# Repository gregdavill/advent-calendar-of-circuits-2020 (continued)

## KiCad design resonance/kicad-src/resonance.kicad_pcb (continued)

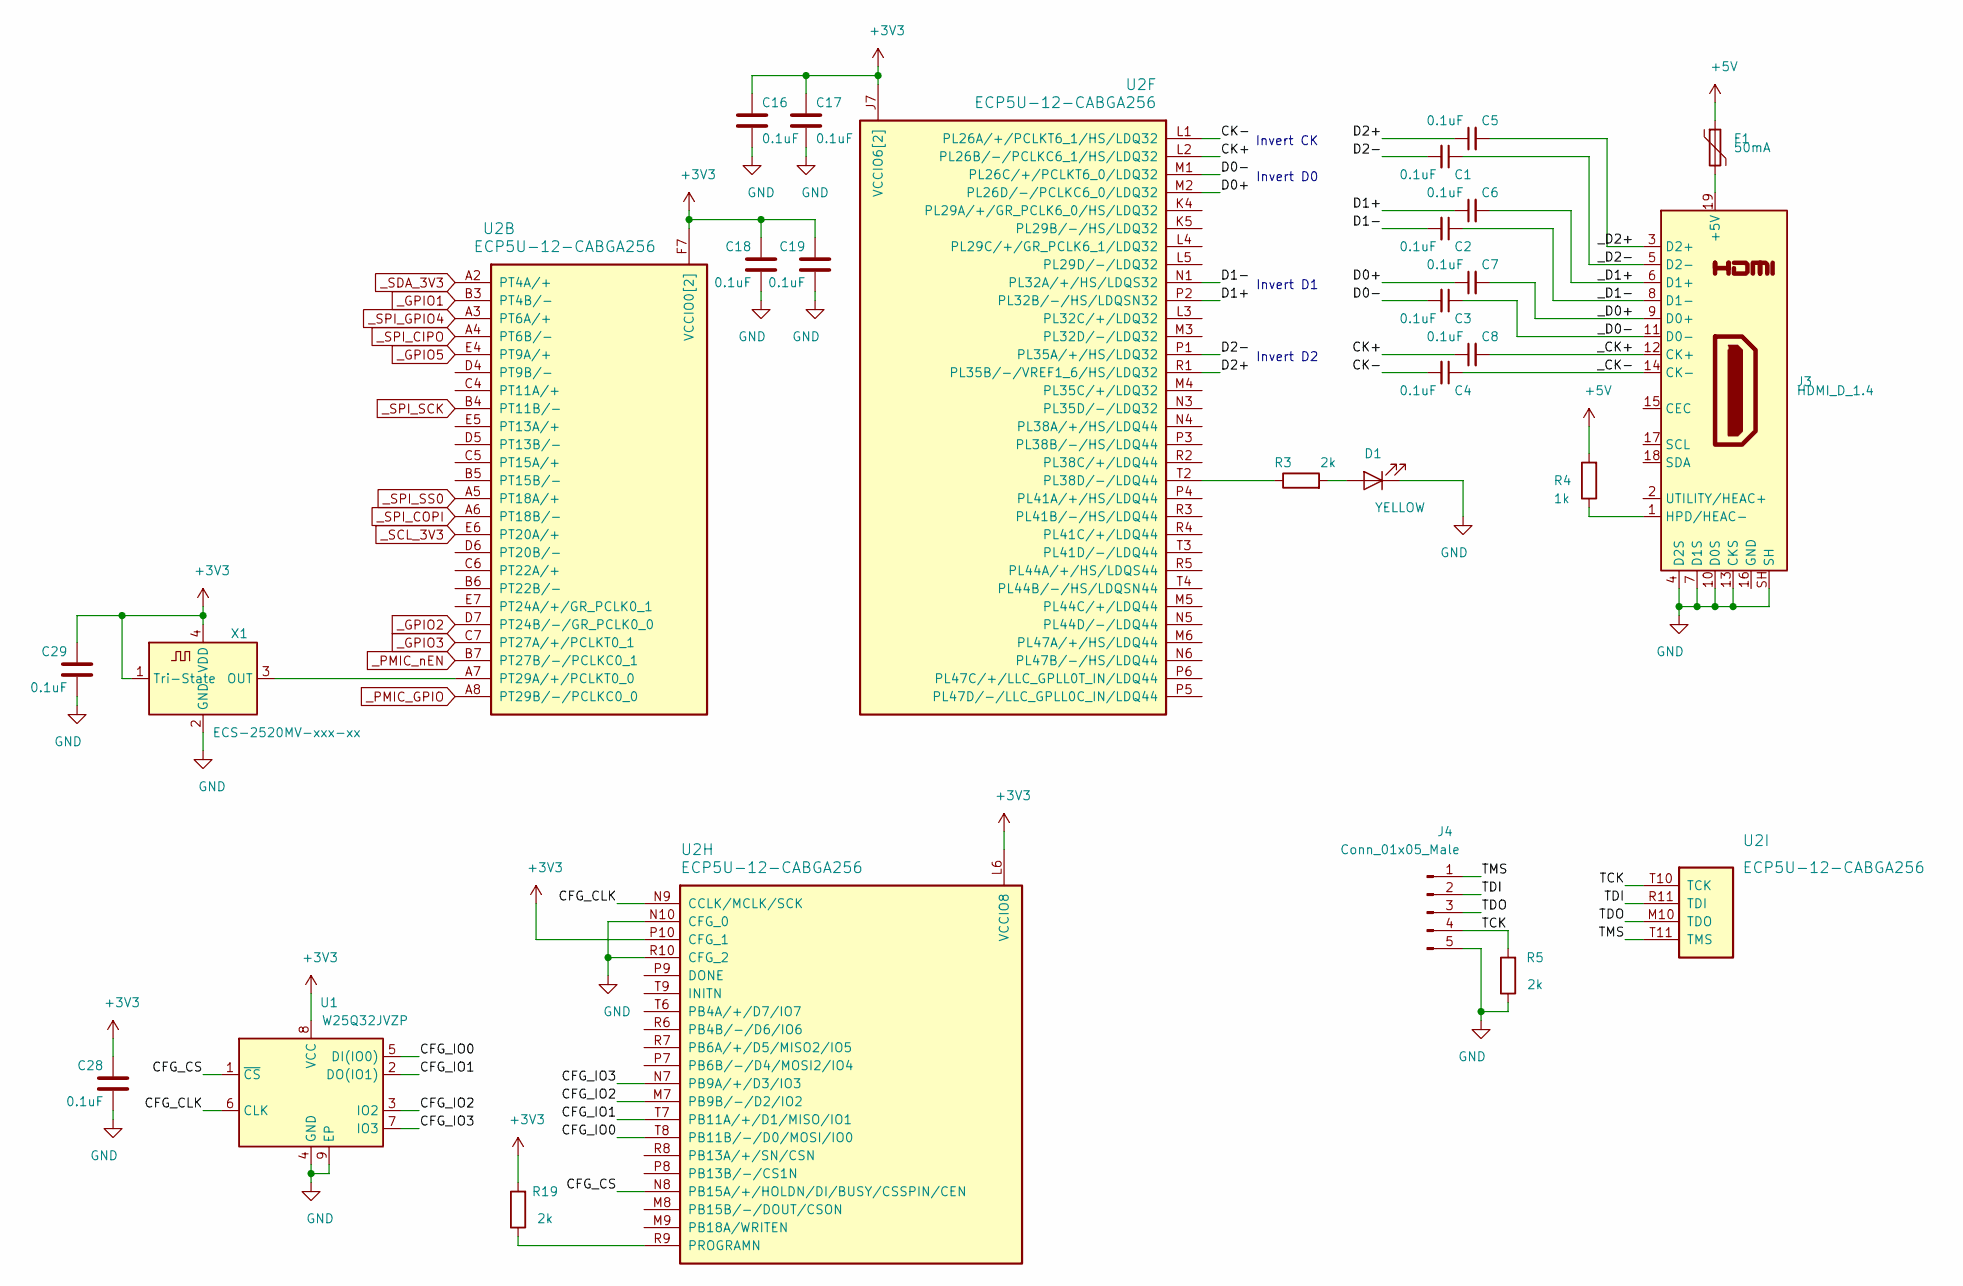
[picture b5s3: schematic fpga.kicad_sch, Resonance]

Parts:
C1, C2, C3, C4, C5, C6, C7, C8, C16, C17, C18, C19, C28, C29: 0.1uF; C_0402_1005Metric
D1: YELLOW; LED_0603_1608Metric
F1: 50mA; Fuse_0805_2012Metric
J3: HDMI_D_1.4; HDMI_Micro-D_Molex_46765-1x01
J4: Conn_01x05_Male; PinHeader_1x05_P2.54mm_Vertical
R3, R5, R19: 2k; R_0402_1005Metric
R4: 1k; R_0402_1005Metric
U1: W25Q32JVZP; WSON-8-1EP_6x5mm_P1.27mm_EP3.4x4.3mm
U2: ECP5U-12-CABGA256; BGA-256_14.0x14.0mm_Layout16x16_P0.8mm_Ball0.45mm_Pad0.32mm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
X1: ECS-2520MV-xxx-xx; Oscillator_SMD_ECS_2520MV-xxx-xx-4Pin_2.5x2.0mm

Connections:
+3V3: C16.1, C17.1, C18.1, C19.1, C28.1, C29.1, R19.2, U1.8 (VCC), U2.F6 (VCCIO0[2]), U2.F7 (VCCIO0[2]), U2.J6 (VCCIO6[2]), U2.J7 (VCCIO6[2]), U2.L6 (VCCIO8), U2.P10 (CFG_1), X1.1 (Tri-State), X1.4 (VDD); also elsewhere on the board
+5V: F1.1, R4.2; also elsewhere on the board
/fpga/CFG_CLK: U1.6 (CLK), U2.N9 (CCLK/MCLK/SCK)
/fpga/CFG_CS: U1.1 (~CS), U2.N8 (PB15A/+/HOLDN/DI/BUSY/CSSPIN/CEN)
/fpga/CFG_IO0: U1.5 (DI(IO0)), U2.T8 (PB11B/-/D0/MOSI/IO0)
/fpga/CFG_IO1: U1.2 (DO(IO1)), U2.T7 (PB11A/+/D1/MISO/IO1)
/fpga/CFG_IO2: U1.3 (IO2), U2.M7 (PB9B/-/D2/IO2)
/fpga/CFG_IO3: U1.7 (IO3), U2.N7 (PB9A/+/D3/IO3)
/fpga/CK+: C8.1, U2.L2 (PL26B/-/PCLKC6_1/HS/LDQ32)
/fpga/CK-: C4.2, U2.L1 (PL26A/+/PCLKT6_1/HS/LDQ32)
/fpga/D0+: C7.1, U2.M2 (PL26D/-/PCLKC6_0/LDQ32)
/fpga/D0-: C3.2, U2.M1 (PL26C/+/PCLKT6_0/LDQ32)
/fpga/D1+: C6.1, U2.P2 (PL32B/-/HS/LDQSN32)
/fpga/D1-: C2.2, U2.N1 (PL32A/+/HS/LDQS32)
/fpga/D2+: C5.1, U2.R1 (PL35B/-/VREF1_6/HS/LDQ32)
/fpga/D2-: C1.2, U2.P1 (PL35A/+/HS/LDQ32)
/fpga/TCK: J4.4, R5.2, U2.T10 (TCK)
/fpga/TDI: J4.2, U2.R11 (TDI)
/fpga/TDO: J4.3, U2.M10 (TDO)
/fpga/TMS: J4.1, U2.T11 (TMS)
/fpga/_CK+: C8.2, J3.12 (CK+)
/fpga/_CK-: C4.1, J3.14 (CK-)
/fpga/_D0+: C7.2, J3.9 (D0+)
/fpga/_D0-: C3.1, J3.11 (D0-)
/fpga/_D1+: C6.2, J3.6 (D1+)
/fpga/_D1-: C2.1, J3.8 (D1-)
/fpga/_D2+: C5.2, J3.3 (D2+)
/fpga/_D2-: C1.1, J3.5 (D2-)
GND: C16.2, C17.2, C18.2, C19.2, C28.2, C29.2, D1.1 (K), J3.4 (D2S), J3.7 (D1S), J3.10 (D0S), J3.13 (CKS), J3.SH, J4.5, R5.1, U1.4 (GND), U1.9 (EP), U2.N10 (CFG_0), U2.R10 (CFG_2), X1.2 (GND); also elsewhere on the board
unnamed: D1.2 (A), R3.2
unnamed: J3.1 (HPD/HEAC-), R4.1
unnamed: F1.2, J3.19 (+5V)
unnamed: U2.A7 (PT29A/+/PCLKT0_0), X1.3 (OUT)
unnamed: R19.1, U2.R9 (PROGRAMN)
unnamed: R3.1, U2.T2 (PL38D/-/LDQ44)
_GPIO1: U2.B3 (PT4B/-); also elsewhere on the board
_GPIO2: U2.D7 (PT24B/-/GR_PCLK0_0); also elsewhere on the board
_GPIO3: U2.C7 (PT27A/+/PCLKT0_1); also elsewhere on the board
_GPIO5: U2.E4 (PT9A/+); also elsewhere on the board
_PMIC_GPIO: U2.A8 (PT29B/-/PCLKC0_0); also elsewhere on the board
_PMIC_nEN: U2.B7 (PT27B/-/PCLKC0_1); also elsewhere on the board
_SCL_3V3: U2.E6 (PT20A/+); also elsewhere on the board
_SDA_3V3: U2.A2 (PT4A/+); also elsewhere on the board
_SPI_CIPO: U2.A4 (PT6B/-); also elsewhere on the board
_SPI_COPI: U2.A6 (PT18B/-); also elsewhere on the board
_SPI_GPIO4: U2.A3 (PT6A/+); also elsewhere on the board
_SPI_SCK: U2.B4 (PT11B/-); also elsewhere on the board
_SPI_SS0: U2.A5 (PT18A/+); also elsewhere on the board

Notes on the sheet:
Invert CK
Invert D0
Invert D1
Invert D2

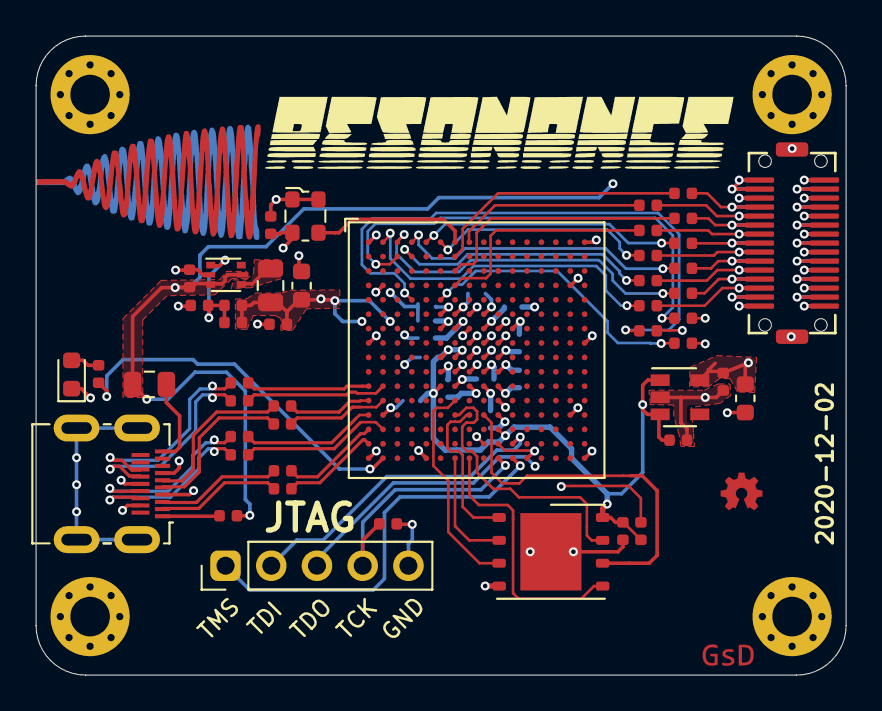
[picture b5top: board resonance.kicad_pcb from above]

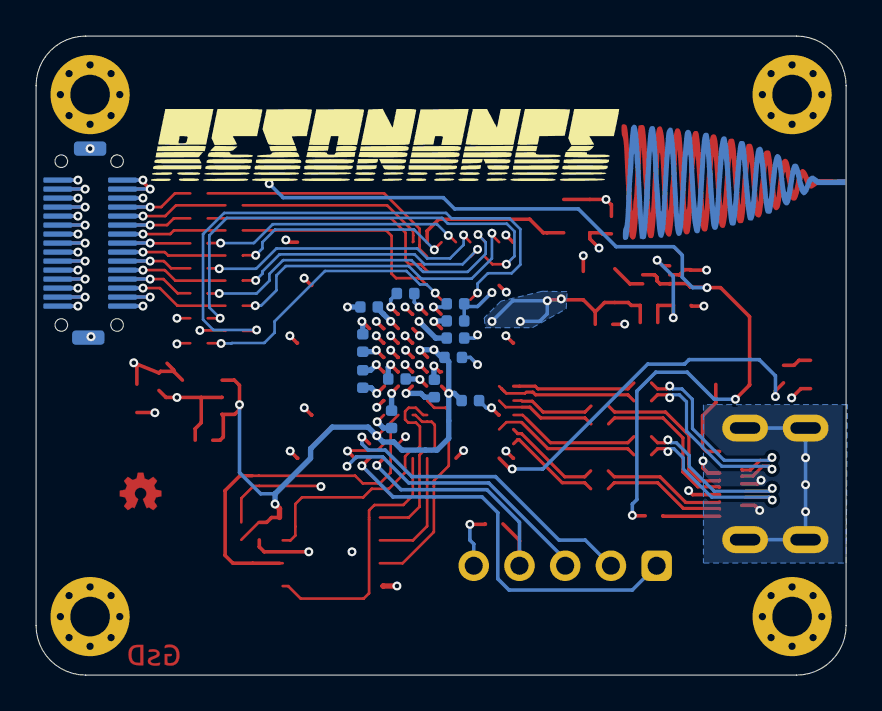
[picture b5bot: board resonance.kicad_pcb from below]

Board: 4 copper layers, 45.0 x 35.5 mm, 66 parts (13 on the bottom side), 75 nets.

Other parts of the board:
H1, H4: ECG_VCM; MountingHole_2.2mm_M2_Pad_Via
H2, H3: MountingHole_Pad; MountingHole_2.2mm_M2_Pad_Via
LOGO1: Q_NMOS_GSD; gsd_logo_small
LOGO2: Logo_Open_Hardware_Small; oshw_small

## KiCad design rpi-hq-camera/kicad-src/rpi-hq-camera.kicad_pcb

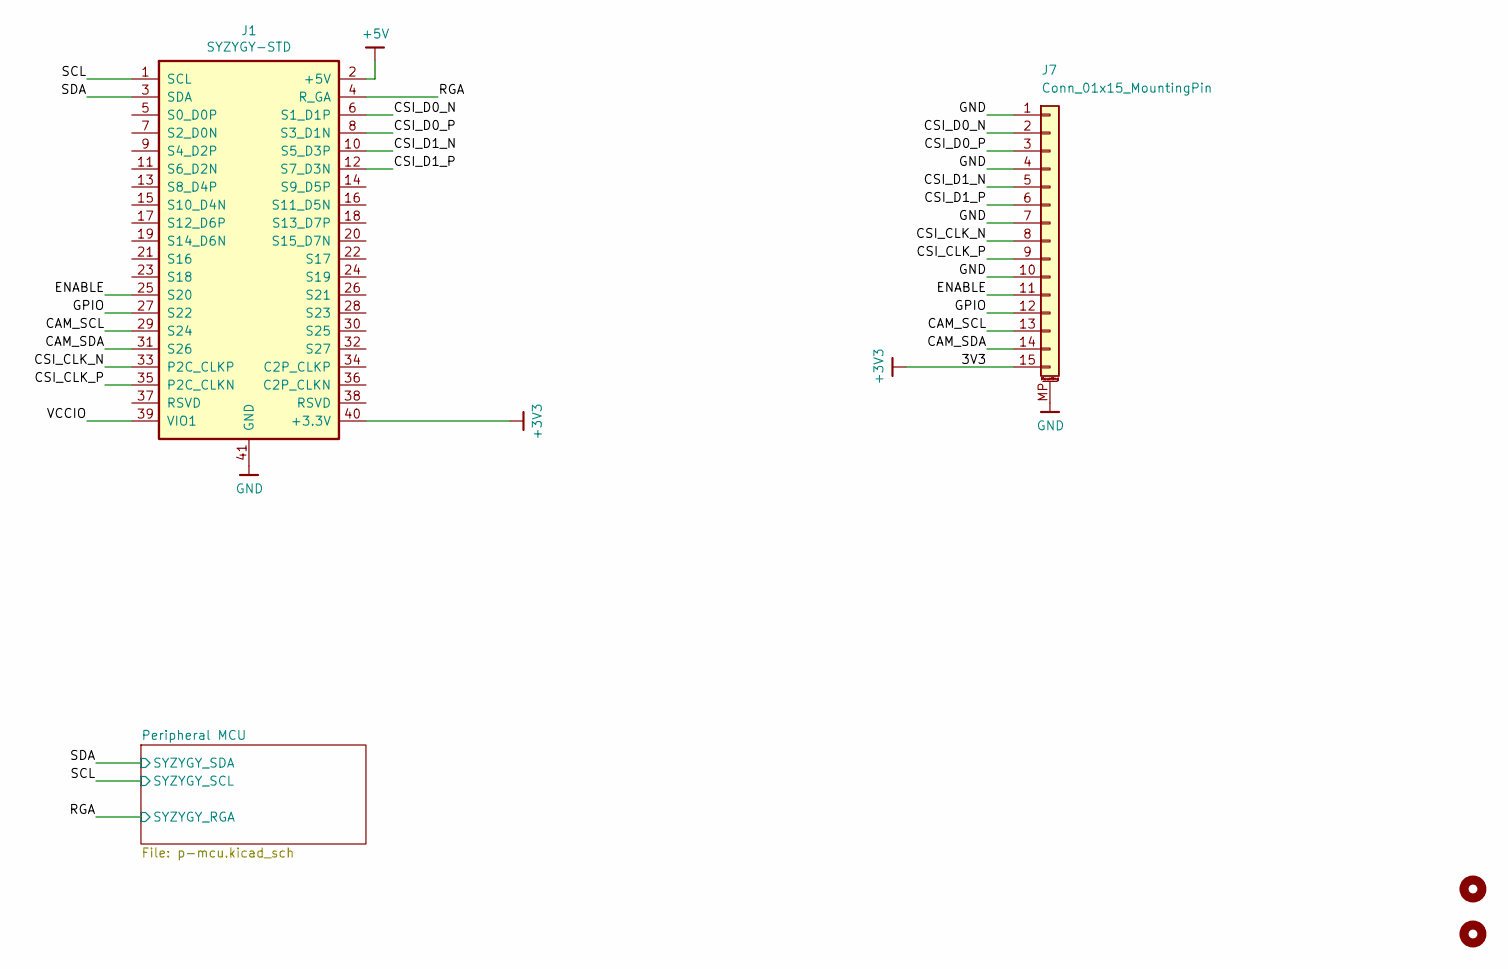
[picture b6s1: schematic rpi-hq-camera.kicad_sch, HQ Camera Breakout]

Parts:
H1, H2: MountingHole; MountingHole_3.2mm_M3_DIN965
J1: SYZYGY-STD; SYZYGY-STD-POD
J7: Conn_01x15_MountingPin; FCI_SFW15R-1STE1LF_1x15-1MP_P1.00mm_Horizontal

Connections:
+3V3: J1.40 (+3.3V), J7.15; also elsewhere on the board
+5V: J1.2 (+5V)
/CAM_SCL: J1.29 (S24), J7.13
/CAM_SDA: J1.31 (S26), J7.14
/CSI_CLK_N: J1.33 (P2C_CLKP), J7.8
/CSI_CLK_P: J1.35 (P2C_CLKN), J7.9
/CSI_D0_N: J1.6 (S1_D1P), J7.2
/CSI_D0_P: J1.8 (S3_D1N), J7.3
/CSI_D1_N: J1.10 (S5_D3P), J7.5
/CSI_D1_P: J1.12 (S7_D3N), J7.6
/ENABLE: J1.25 (S20), J7.11
/GPIO: J1.27 (S22), J7.12
/RGA: J1.4 (R_GA); also elsewhere on the board
/SCL: J1.1 (SCL); also elsewhere on the board
/SDA: J1.3 (SDA); also elsewhere on the board
/VCCIO: J1.39 (VIO1)
GND: J1.41 (GND), J7.1, J7.4, J7.7, J7.10, J7.MP (MountPin); also elsewhere on the board

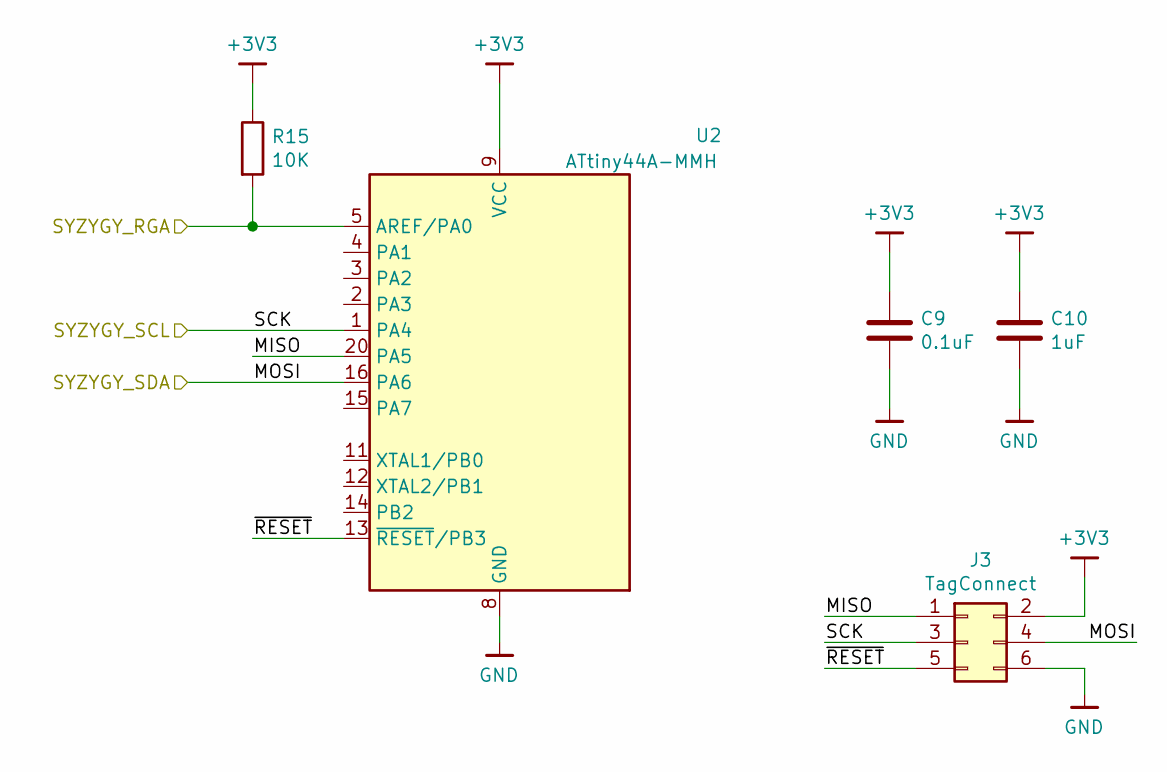
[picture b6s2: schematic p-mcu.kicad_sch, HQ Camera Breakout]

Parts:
C9: 0.1uF; C_0402_1005Metric
C10: 1uF; C_0402_1005Metric
J3: TagConnect; TC2030-NL_SMALL
R15: 10K; R_0402_1005Metric
U2: ATtiny44A-MMH; QFN-20-1EP_3x3mm_P0.45mm_EP1.6x1.6mm

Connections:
+3V3: C9.1, C10.1, J3.2, R15.1, U2.9 (VCC); also elsewhere on the board
/Peripheral MCU/MISO: J3.1, U2.20 (PA5)
/Peripheral MCU/~RESET: J3.5, U2.13 (~RESET~/PB3)
/RGA: R15.2, U2.5 (AREF/PA0); also elsewhere on the board
/SCL: J3.3, U2.1 (PA4); also elsewhere on the board
/SDA: J3.4, U2.16 (PA6); also elsewhere on the board
GND: C9.2, C10.2, J3.6, U2.8 (GND), U2.21 (GND); also elsewhere on the board
no_connect_51: U2.10 (NC)
no_connect_52: U2.17 (NC)
no_connect_53: U2.18 (NC)
no_connect_54: U2.19 (NC)
no_connect_55: U2.6 (NC)
no_connect_56: U2.7 (NC)

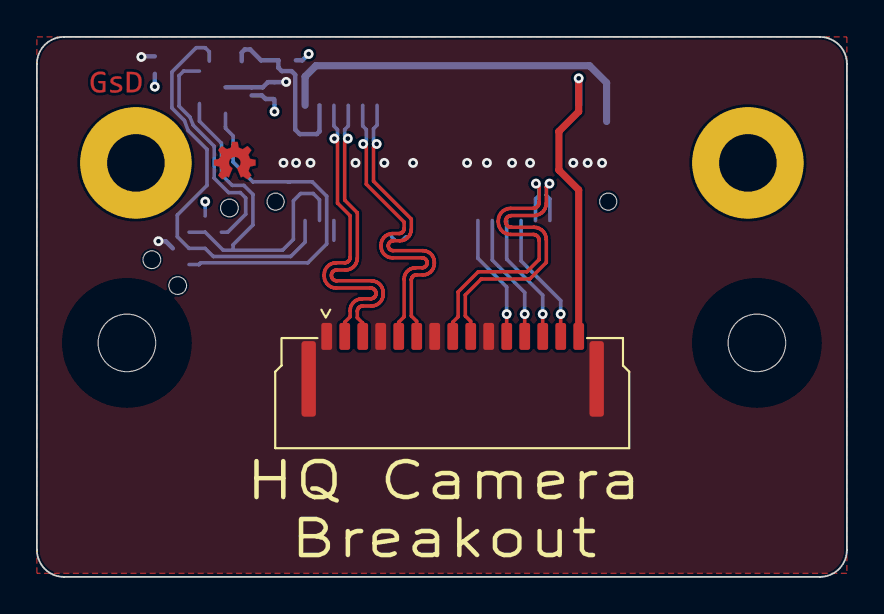
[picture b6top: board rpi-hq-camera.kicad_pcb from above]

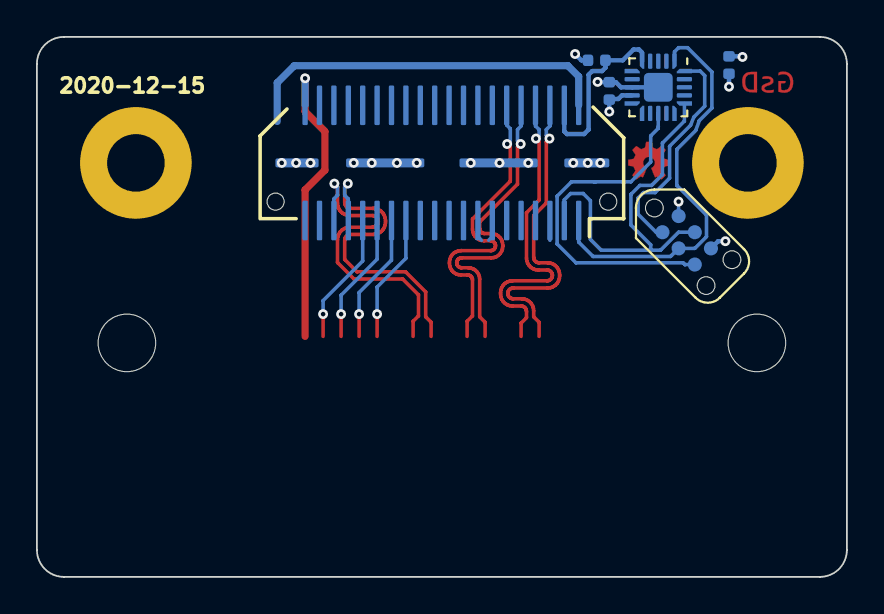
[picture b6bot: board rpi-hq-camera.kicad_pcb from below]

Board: 4 copper layers, 45.0 x 30.0 mm, 9 parts (6 on the bottom side), 17 nets.

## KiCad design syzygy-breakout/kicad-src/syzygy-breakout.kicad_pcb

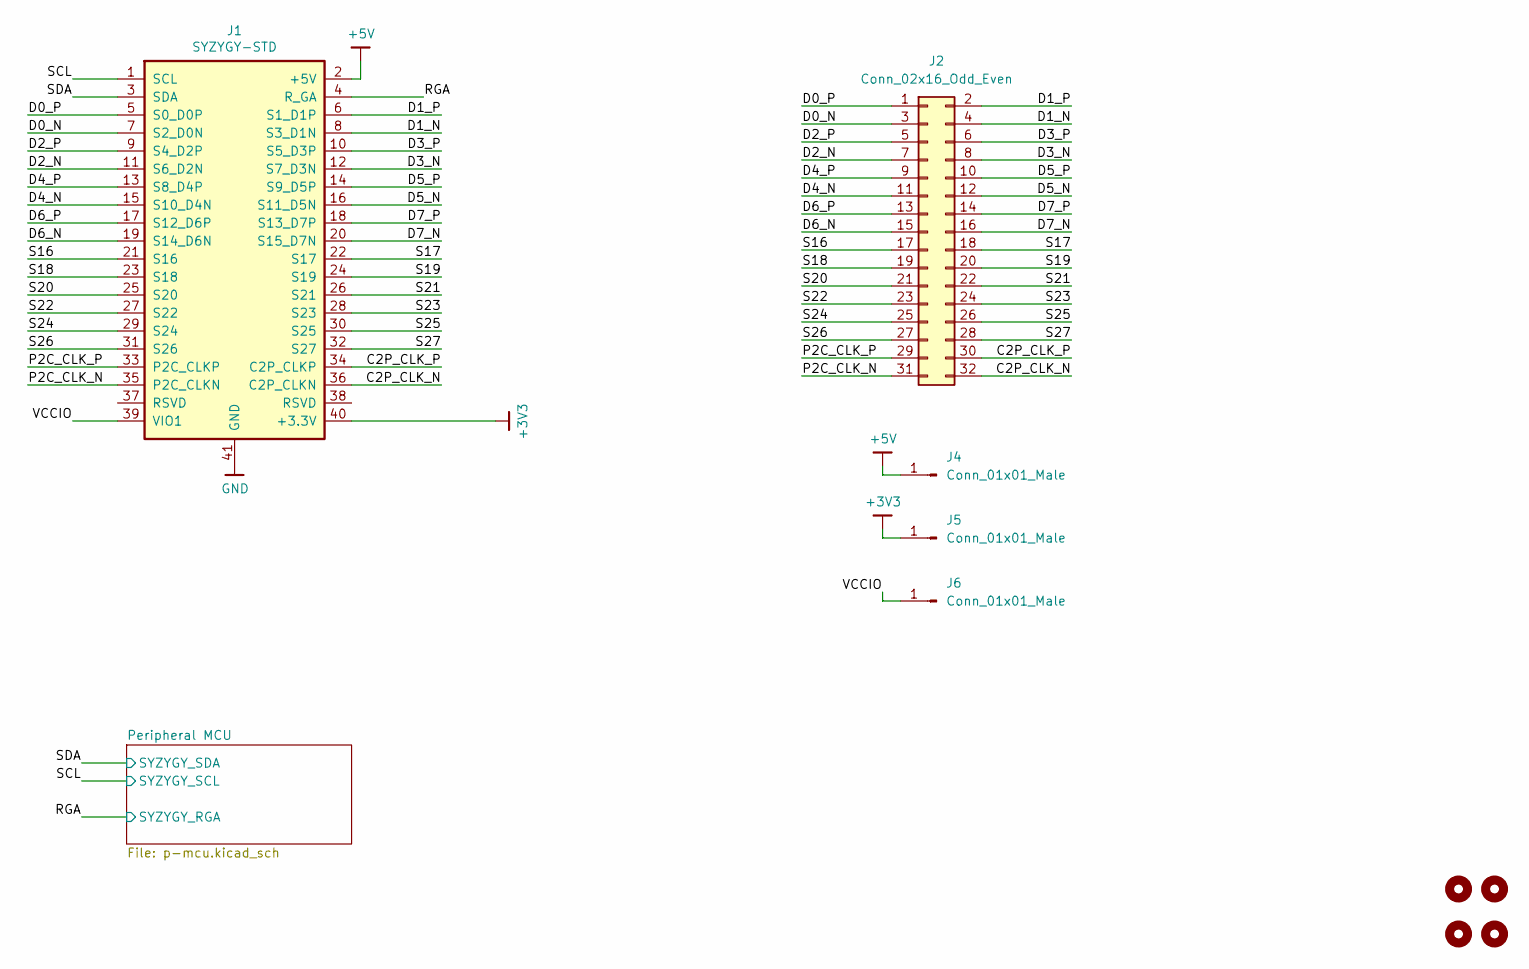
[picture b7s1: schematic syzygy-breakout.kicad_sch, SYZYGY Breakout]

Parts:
H1, H2, H3, H4: MountingHole; MountingHole_3.2mm_M3_DIN965
J1: SYZYGY-STD; SYZYGY-STD-POD
J2: Conn_02x16_Odd_Even; PinHeader_2x16_P2.54mm_Vertical
J4, J5, J6: Conn_01x01_Male; PinHeader_1x01_P2.54mm_Vertical

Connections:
+3V3: J1.40 (+3.3V), J5.1; also elsewhere on the board
+5V: J1.2 (+5V), J4.1
/C2P_CLK_N: J1.36 (C2P_CLKN), J2.32
/C2P_CLK_P: J1.34 (C2P_CLKP), J2.30
/D0_N: J1.7 (S2_D0N), J2.3
/D0_P: J1.5 (S0_D0P), J2.1
/D1_N: J1.8 (S3_D1N), J2.4
/D1_P: J1.6 (S1_D1P), J2.2
/D2_N: J1.11 (S6_D2N), J2.7
/D2_P: J1.9 (S4_D2P), J2.5
/D3_N: J1.12 (S7_D3N), J2.8
/D3_P: J1.10 (S5_D3P), J2.6
/D4_N: J1.15 (S10_D4N), J2.11
/D4_P: J1.13 (S8_D4P), J2.9
/D5_N: J1.16 (S11_D5N), J2.12
/D5_P: J1.14 (S9_D5P), J2.10
/D6_N: J1.19 (S14_D6N), J2.15
/D6_P: J1.17 (S12_D6P), J2.13
/D7_N: J1.20 (S15_D7N), J2.16
/D7_P: J1.18 (S13_D7P), J2.14
/P2C_CLK_N: J1.35 (P2C_CLKN), J2.31
/P2C_CLK_P: J1.33 (P2C_CLKP), J2.29
/RGA: J1.4 (R_GA); also elsewhere on the board
/S16: J1.21 (S16), J2.17
/S17: J1.22 (S17), J2.18
/S18: J1.23 (S18), J2.19
/S19: J1.24 (S19), J2.20
/S20: J1.25 (S20), J2.21
/S21: J1.26 (S21), J2.22
/S22: J1.27 (S22), J2.23
/S23: J1.28 (S23), J2.24
/S24: J1.29 (S24), J2.25
/S25: J1.30 (S25), J2.26
/S26: J1.31 (S26), J2.27
/S27: J1.32 (S27), J2.28
/SCL: J1.1 (SCL); also elsewhere on the board
/SDA: J1.3 (SDA); also elsewhere on the board
/VCCIO: J1.39 (VIO1), J6.1
GND: J1.41 (GND); also elsewhere on the board

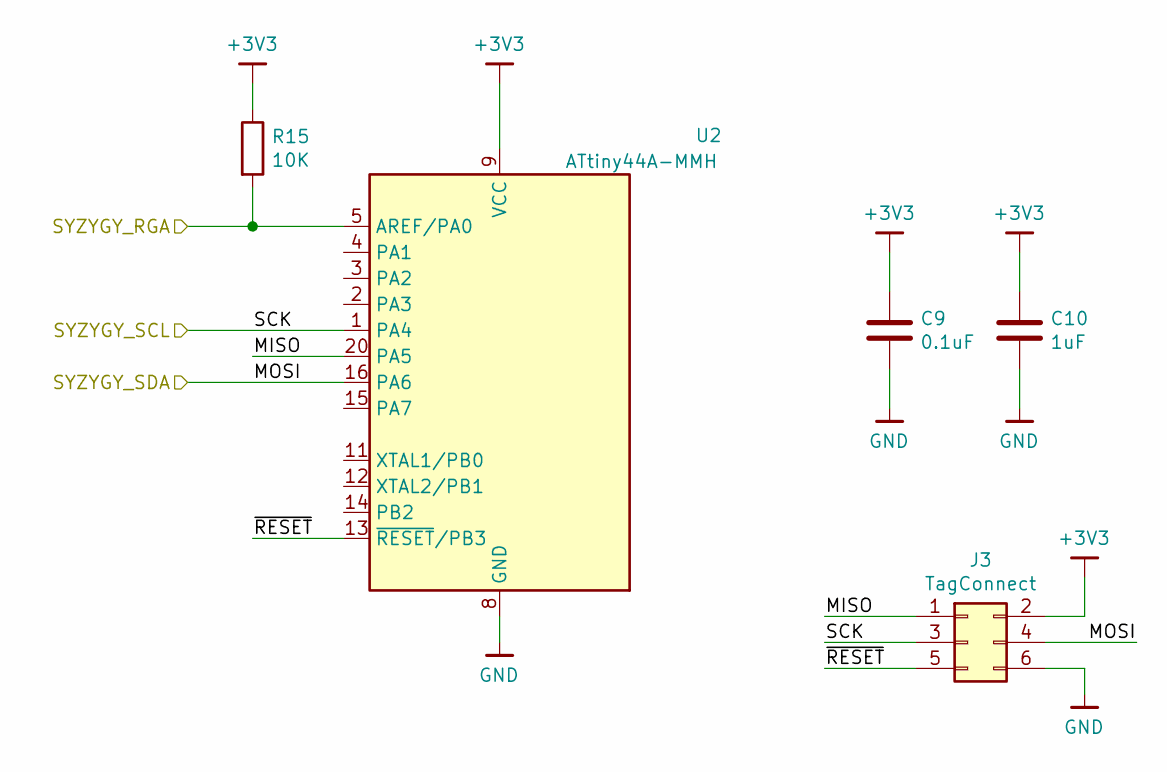
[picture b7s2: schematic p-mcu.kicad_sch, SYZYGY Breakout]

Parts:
C9: 0.1uF; C_0402_1005Metric
C10: 1uF; C_0402_1005Metric
J3: TagConnect; TC2030-NL_SMALL
R15: 10K; R_0402_1005Metric
U2: ATtiny44A-MMH; QFN-20-1EP_3x3mm_P0.45mm_EP1.6x1.6mm

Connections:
+3V3: C9.1, C10.1, J3.2, R15.1, U2.9 (VCC); also elsewhere on the board
/Peripheral MCU/MISO: J3.1, U2.20 (PA5)
/Peripheral MCU/~RESET: J3.5, U2.13 (~RESET~/PB3)
/RGA: R15.2, U2.5 (AREF/PA0); also elsewhere on the board
/SCL: J3.3, U2.1 (PA4); also elsewhere on the board
/SDA: J3.4, U2.16 (PA6); also elsewhere on the board
GND: C9.2, C10.2, J3.6, U2.8 (GND), U2.21 (GND); also elsewhere on the board
no_connect_51: U2.10 (NC)
no_connect_52: U2.17 (NC)
no_connect_53: U2.18 (NC)
no_connect_54: U2.19 (NC)
no_connect_55: U2.6 (NC)
no_connect_56: U2.7 (NC)

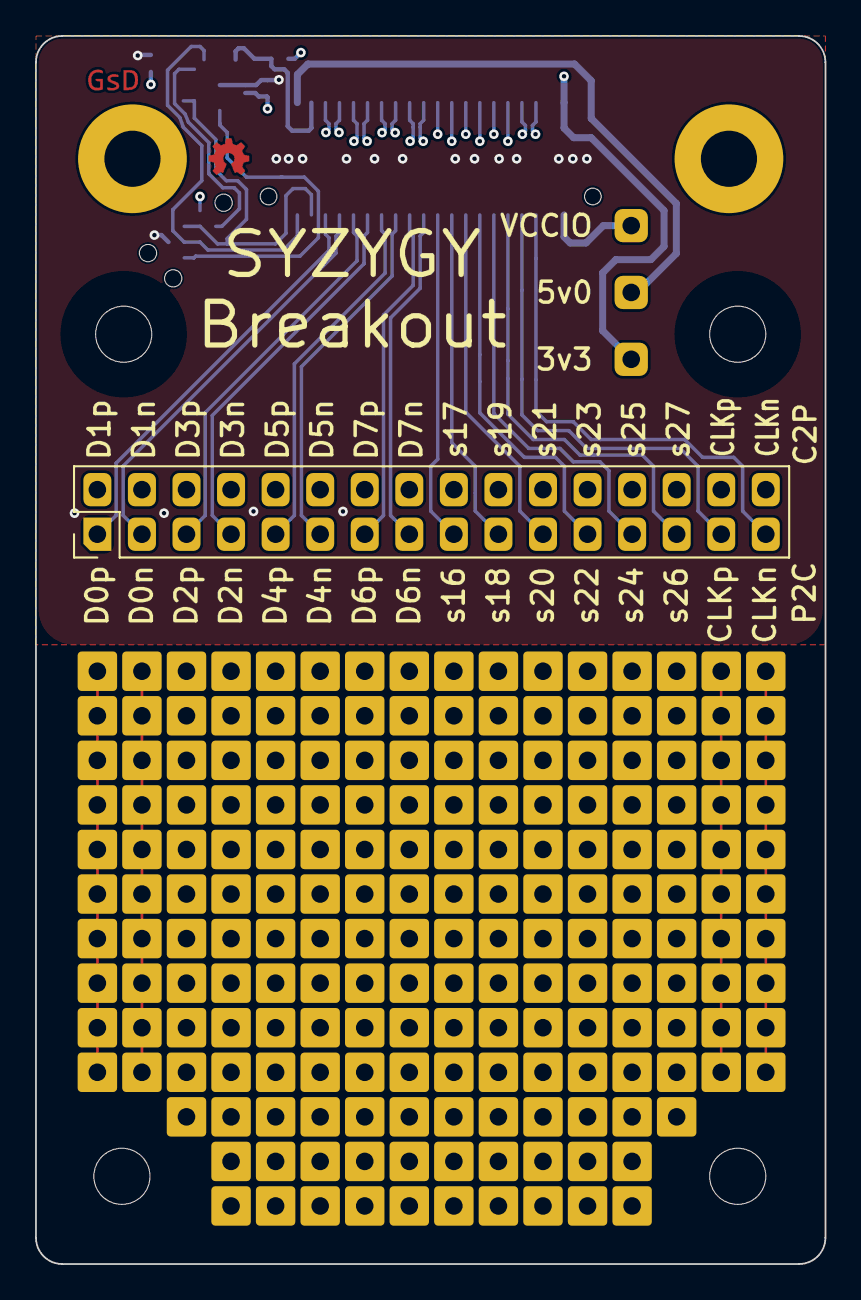
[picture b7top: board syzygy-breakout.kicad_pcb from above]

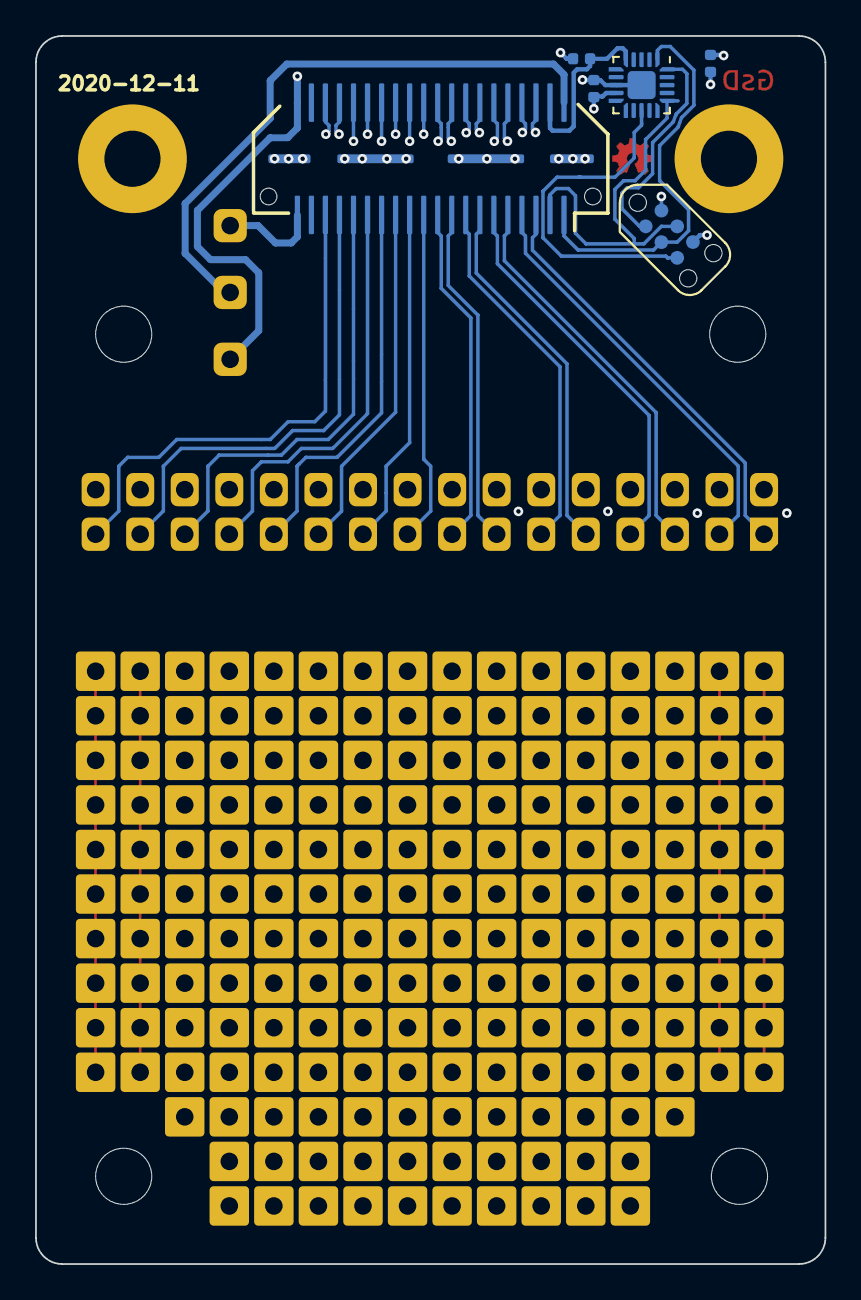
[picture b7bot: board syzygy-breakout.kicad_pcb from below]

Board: 4 copper layers, 45.0 x 70.0 mm, 14 parts (6 on the bottom side), 41 nets.

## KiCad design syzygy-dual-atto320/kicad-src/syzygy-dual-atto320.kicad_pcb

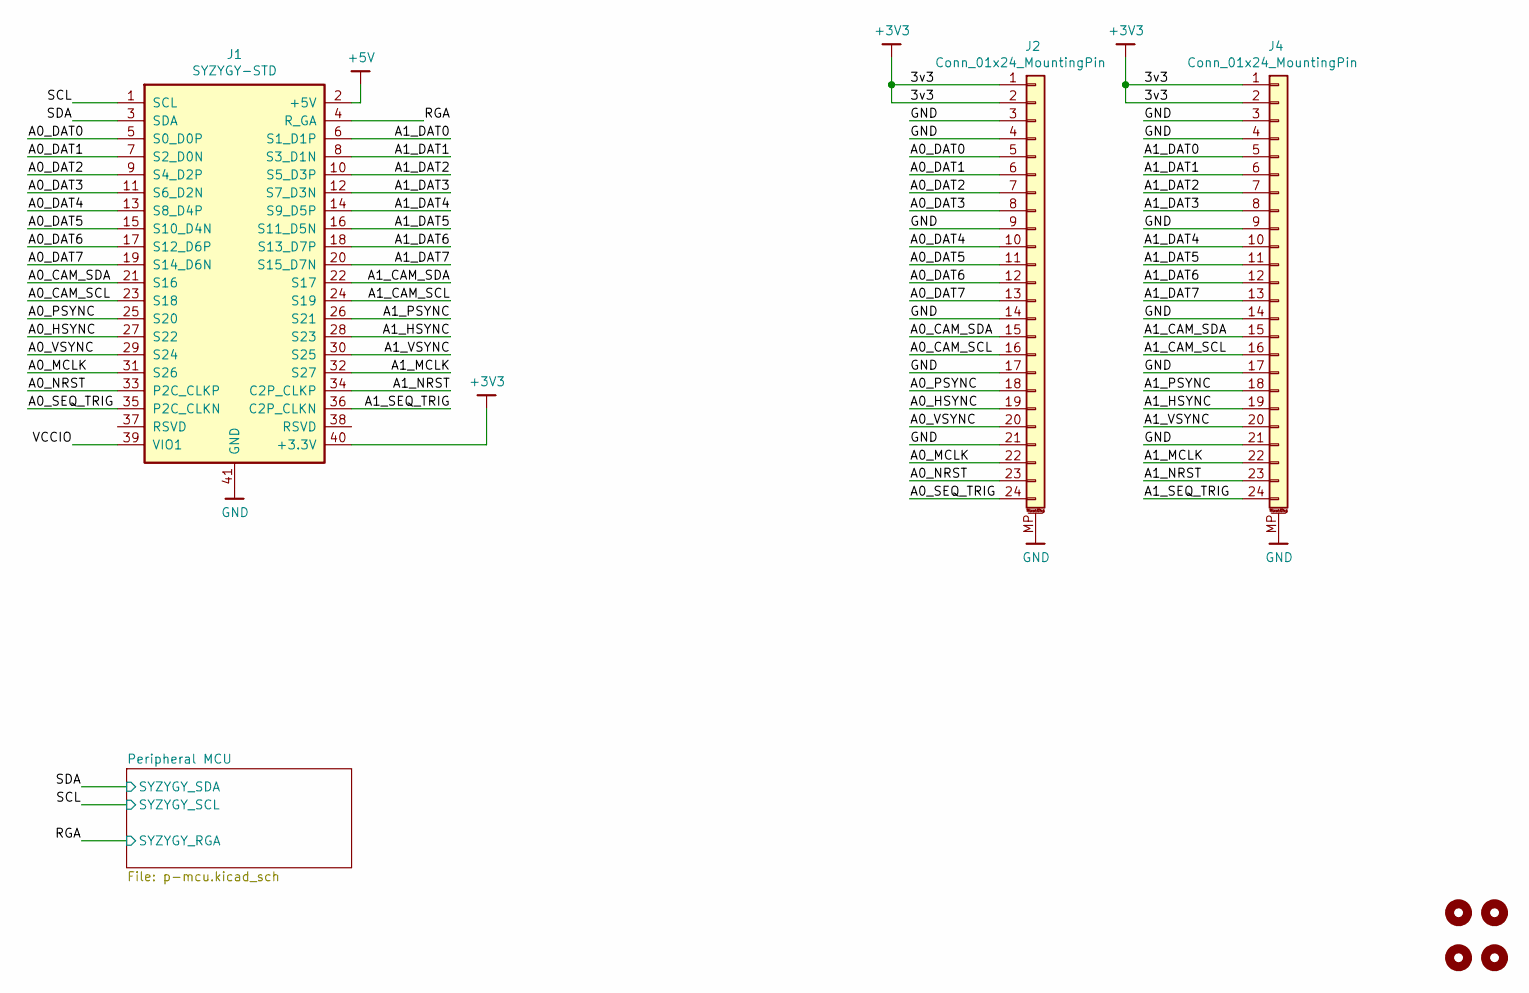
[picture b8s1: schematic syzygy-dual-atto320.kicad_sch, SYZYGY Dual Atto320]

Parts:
H1, H2, H3, H4: MountingHole; MountingHole_3.2mm_M3_DIN965
J1: SYZYGY-STD; SYZYGY-STD-POD
J2, J4: Conn_01x24_MountingPin; XF2M-2415-1A

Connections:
+3V3: J1.40 (+3.3V), J2.1, J2.2, J4.1, J4.2; also elsewhere on the board
+5V: J1.2 (+5V)
/A0_CAM_SCL: J1.23 (S18), J2.16
/A0_CAM_SDA: J1.21 (S16), J2.15
/A0_DAT0: J1.5 (S0_D0P), J2.5
/A0_DAT1: J1.7 (S2_D0N), J2.6
/A0_DAT2: J1.9 (S4_D2P), J2.7
/A0_DAT3: J1.11 (S6_D2N), J2.8
/A0_DAT4: J1.13 (S8_D4P), J2.10
/A0_DAT5: J1.15 (S10_D4N), J2.11
/A0_DAT6: J1.17 (S12_D6P), J2.12
/A0_DAT7: J1.19 (S14_D6N), J2.13
/A0_HSYNC: J1.27 (S22), J2.19
/A0_MCLK: J1.31 (S26), J2.22
/A0_NRST: J1.33 (P2C_CLKP), J2.23
/A0_PSYNC: J1.25 (S20), J2.18
/A0_SEQ_TRIG: J1.35 (P2C_CLKN), J2.24
/A0_VSYNC: J1.29 (S24), J2.20
/A1_CAM_SCL: J1.24 (S19), J4.16
/A1_CAM_SDA: J1.22 (S17), J4.15
/A1_DAT0: J1.6 (S1_D1P), J4.5
/A1_DAT1: J1.8 (S3_D1N), J4.6
/A1_DAT2: J1.10 (S5_D3P), J4.7
/A1_DAT3: J1.12 (S7_D3N), J4.8
/A1_DAT4: J1.14 (S9_D5P), J4.10
/A1_DAT5: J1.16 (S11_D5N), J4.11
/A1_DAT6: J1.18 (S13_D7P), J4.12
/A1_DAT7: J1.20 (S15_D7N), J4.13
/A1_HSYNC: J1.28 (S23), J4.19
/A1_MCLK: J1.32 (S27), J4.22
/A1_NRST: J1.34 (C2P_CLKP), J4.23
/A1_PSYNC: J1.26 (S21), J4.18
/A1_SEQ_TRIG: J1.36 (C2P_CLKN), J4.24
/A1_VSYNC: J1.30 (S25), J4.20
/RGA: J1.4 (R_GA); also elsewhere on the board
/SCL: J1.1 (SCL); also elsewhere on the board
/SDA: J1.3 (SDA); also elsewhere on the board
/VCCIO: J1.39 (VIO1)
GND: J1.41 (GND), J2.3, J2.4, J2.9, J2.14, J2.17, J2.21, J2.MP (MountPin), J4.3, J4.4, J4.9, J4.14, J4.17, J4.21, J4.MP (MountPin); also elsewhere on the board

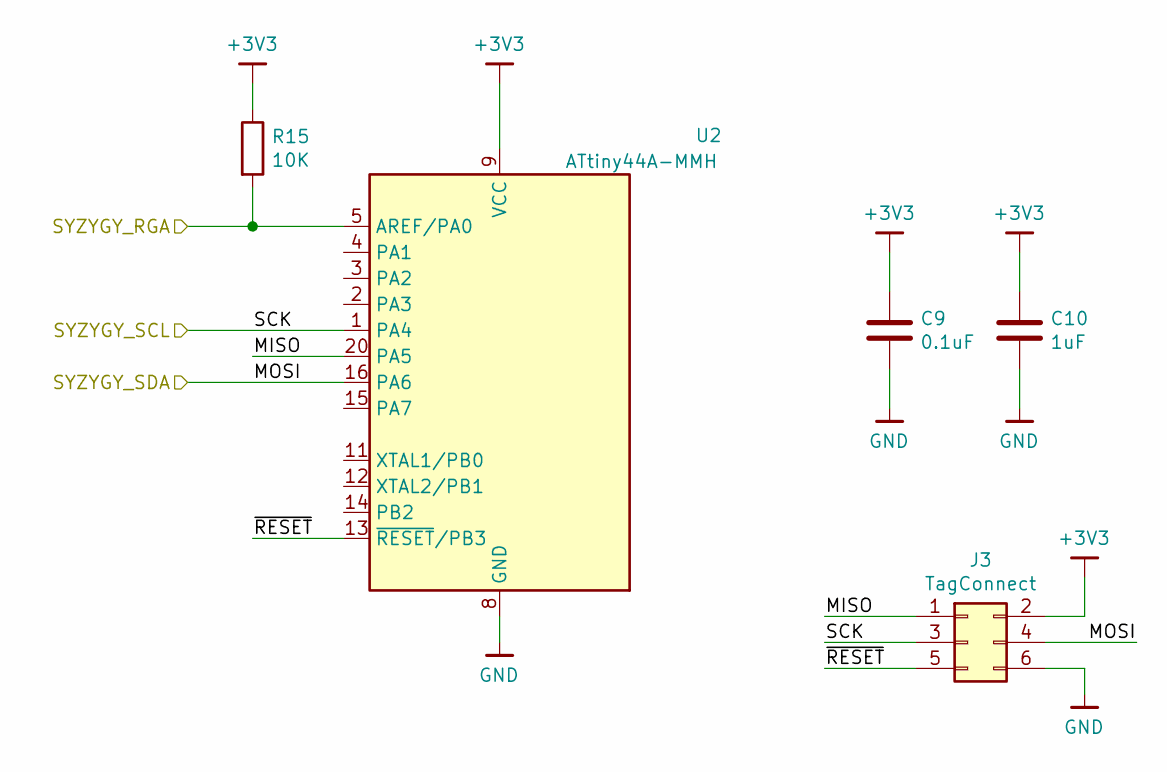
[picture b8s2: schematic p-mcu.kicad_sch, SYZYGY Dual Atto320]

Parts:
C9: 0.1uF; C_0402_1005Metric
C10: 1uF; C_0402_1005Metric
J3: TagConnect; TC2030-NL_SMALL
R15: 10K; R_0402_1005Metric
U2: ATtiny44A-MMH; QFN-20-1EP_3x3mm_P0.45mm_EP1.6x1.6mm

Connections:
+3V3: C9.1, C10.1, J3.2, R15.1, U2.9 (VCC); also elsewhere on the board
/Peripheral MCU/MISO: J3.1, U2.20 (PA5)
/Peripheral MCU/~RESET: J3.5, U2.13 (~RESET~/PB3)
/RGA: R15.2, U2.5 (AREF/PA0); also elsewhere on the board
/SCL: J3.3, U2.1 (PA4); also elsewhere on the board
/SDA: J3.4, U2.16 (PA6); also elsewhere on the board
GND: C9.2, C10.2, J3.6, U2.8 (GND), U2.21 (GND); also elsewhere on the board
no_connect_51: U2.10 (NC)
no_connect_52: U2.17 (NC)
no_connect_53: U2.18 (NC)
no_connect_54: U2.19 (NC)
no_connect_55: U2.6 (NC)
no_connect_56: U2.7 (NC)

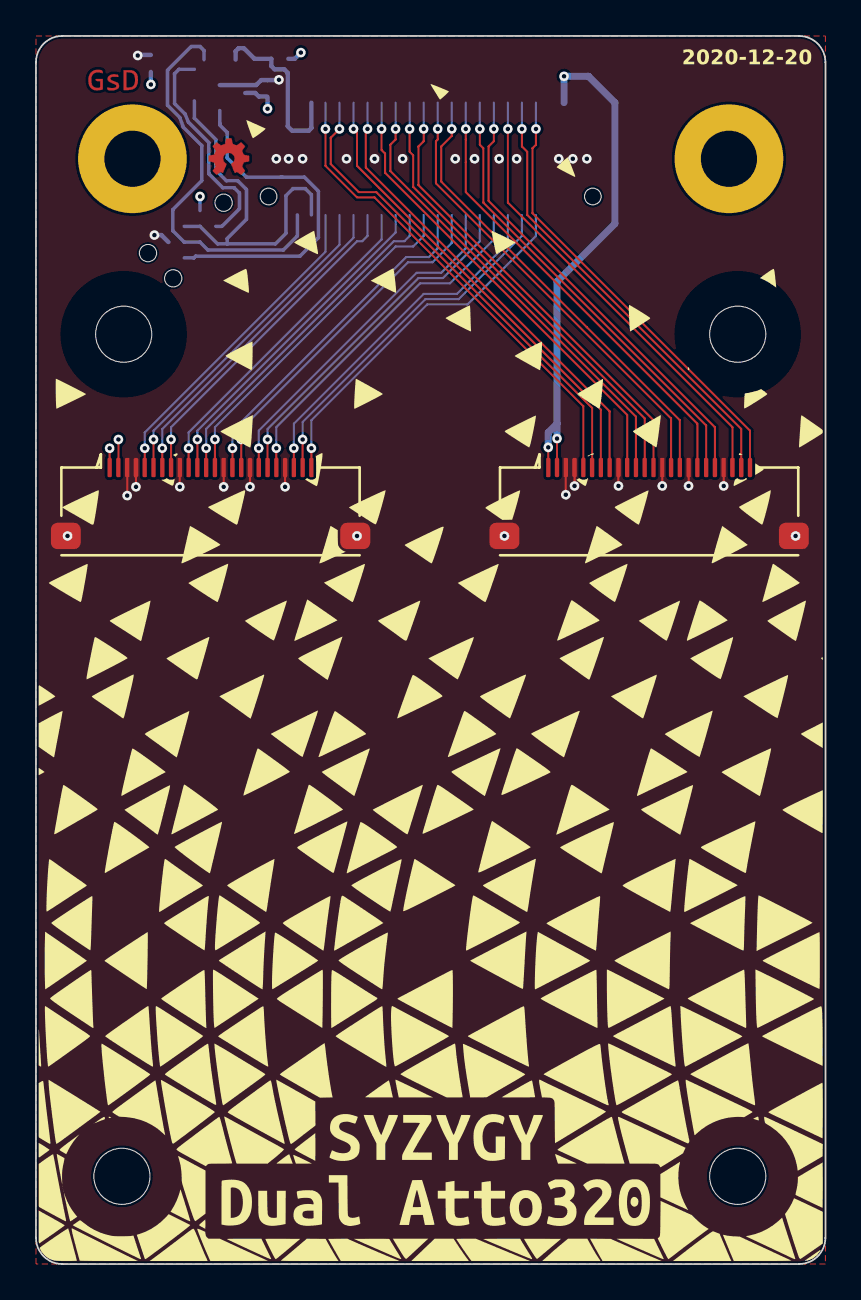
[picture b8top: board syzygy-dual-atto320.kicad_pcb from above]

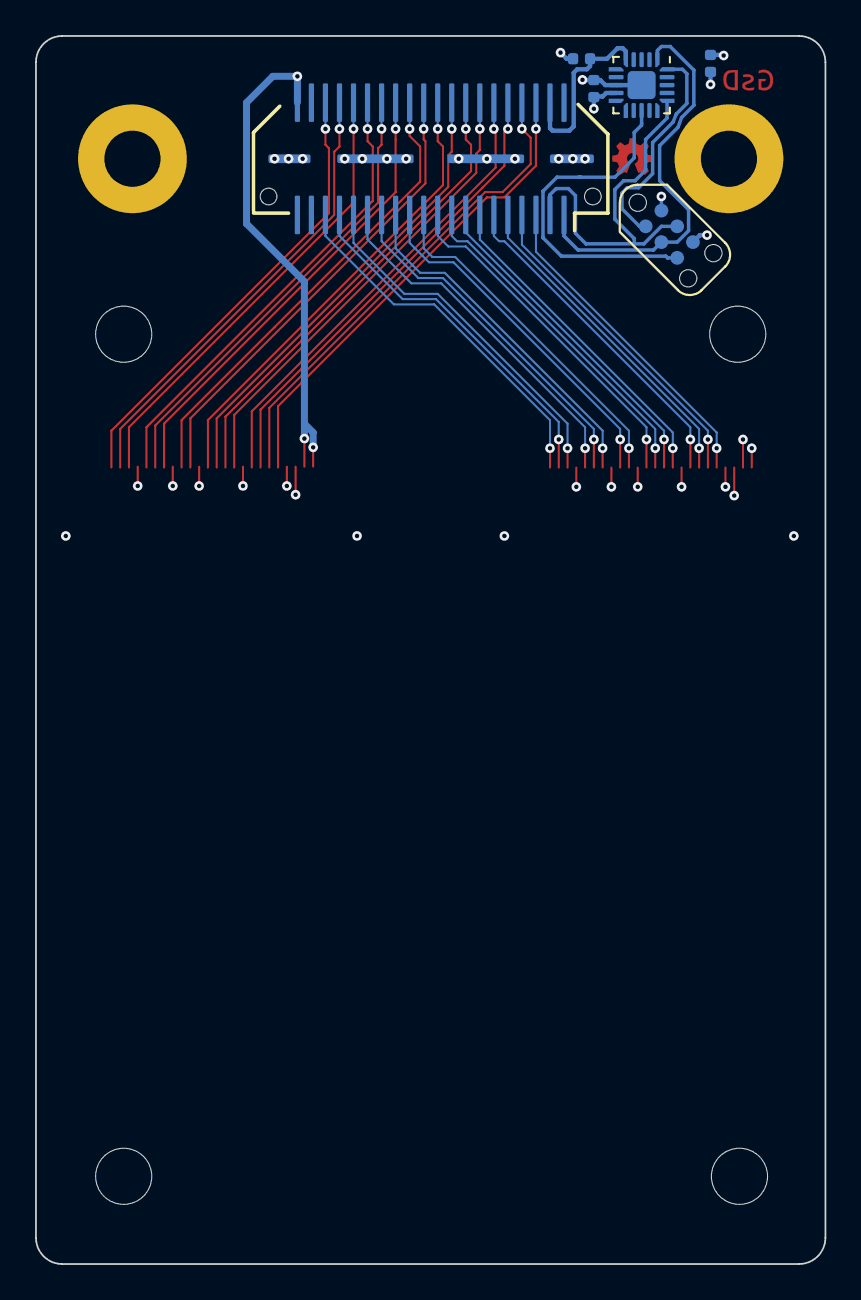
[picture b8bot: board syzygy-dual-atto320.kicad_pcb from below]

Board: 4 copper layers, 45.0 x 70.0 mm, 12 parts (6 on the bottom side), 39 nets.
